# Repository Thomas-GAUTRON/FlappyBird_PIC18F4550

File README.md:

# Projet Flappy Bird PIC18F4550
Membre du projet:
 - BEAUGEANT Clément 
 - CHAUDEMANCHE Nicolas
 - COLIN Malo
 - GAUTRON Thomas 

##  Description du projet
Flappic-Bird est une réimplémentation du jeu **Flappy Bird** sur une carte de développement **EasyPIC v7**. Le jeu utilise plusieurs capteurs pour contrôler le mouvement de l’oiseau et affiche l’interface graphique via une communication UART entre la carte et un PC.

### Objectifs
- Implémenter les mécaniques de base du jeu (gravité, saut, détection de collisions).
- Comparer la précision et le temps de réponse de différents capteurs :
  - Encodeur numérique
  - Bouton poussoir
  - Capteur à ultrasons (HC-SR04)
  - Capteur infrarouge (IR Distance Click)
- Développer une interface graphique en Python
- Enregistrer les meilleurs scores en EEPROM.
- Mode "replay" pour revivre la dernière partie.

## Fonctionnalités
- **4 modes de contrôle** (encodeur, bouton, ultrasons, IR).
- **Menu interactif** (Jouer, Instructions, Replay).
- **Affichage du score** sur des affichages 7-segments et un buzzer.
- **Communication USB** entre la carte EasyPIC et le PC.
- **Mode replay** pour visualiser la dernière partie en accéléré.
- **Aspect ratio** étudié pour optimiser l’apprentissage d’un algorithme génétique (NEAT).

## 🛠 Matériel requis
- **Carte EasyPIC v7** ([manuel](https://download.mikroe.com/documents/full-featured-boards/easy/easypic-v7/easypic-v7-manual-v104c.pdf))
- **Capteurs** :
  - Encodeur numérique
  - Bouton poussoir
  - HC-SR04 (ultrasons)
  - IR Distance Click ([lien](https://www.mikroe.com/ir-distance-click))
- **Affichage** :
  - GLCD (pour l’angle de l’oiseau)
  - 7-segments (pour le score)
- **Buzzer** pour les effets sonores.
- **PC** pour l’interface graphique (Python).

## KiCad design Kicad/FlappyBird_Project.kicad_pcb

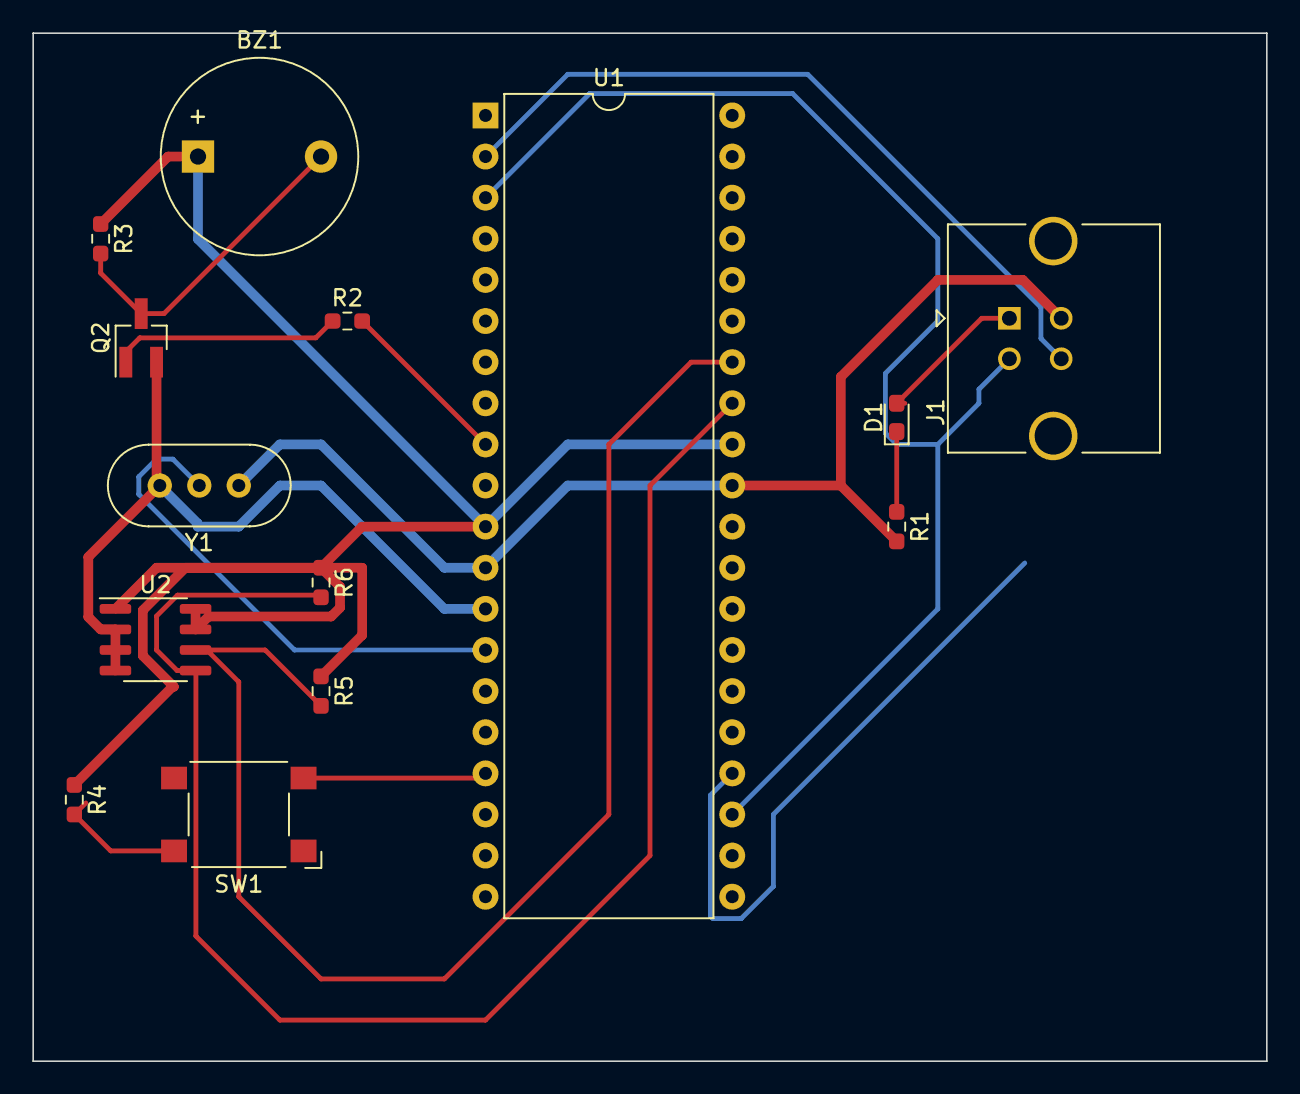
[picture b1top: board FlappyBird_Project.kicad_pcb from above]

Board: 2 copper layers, 76.2 x 63.5 mm, 14 parts (0 on the bottom side), 14 nets.

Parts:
BZ1: Buzzer; Buzzer_12x9.5RM7.6
D1: LED; LED_0603_1608Metric_Pad1.05x0.95mm_HandSolder
J1: USB_B; USB_B_Amphenol_MUSB-D511_Vertical_Rugged
Q2: BC846; SOT-23_Handsoldering
R1: 4K7; R_0603_1608Metric_Pad0.98x0.95mm_HandSolder
R2: 10K; R_0603_1608Metric_Pad0.98x0.95mm_HandSolder
R3, R5, R6: 1K; R_0603_1608Metric_Pad0.98x0.95mm_HandSolder
R4: 220; R_0603_1608Metric_Pad0.98x0.95mm_HandSolder
SW1: SW_Omron_B3FS; SW_SPST_Omron_B3FS-100xP
U1: PIC18F4550-IP; DIP-40_W15.24mm
U2: M24C02-WMN; SOIC-8_3.9x4.9mm_P1.27mm
Y1: Crystal_GND3; Crystal_HC49-U-3Pin_Vertical

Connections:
GND: J1.4 (GND), Q2.2 (E), R1.2, U1.12 (VSS), U1.13 (OSC1/CLKI), U1.31 (VSS), U2.2 (E1), U2.3 (E2), U2.4 (VSS), Y1.1, Y1.3
unnamed: BZ1.2 (+), Q2.3 (C), R3.2
unnamed: D1.2 (A), J1.1 (VBUS)
unnamed: D1.1 (K), R1.1
unnamed: J1.3 (D+), U1.2 (RA0/AN0), U1.24 (VP/D+/RC5)
unnamed: J1.2 (D-), U1.3 (RA1/AN1), U1.23 (VM/D-/RC4)
unnamed: Q2.1 (B), R2.1
unnamed: R4.2, SW1.1
unnamed: R2.2, U1.9 (CK2SPP/AN6/RE1)
unnamed: SW1.2, U1.17 (P1A/CCP1/RC2)
unnamed: U1.14 (RA6/OSC2/CLKO), Y1.2
unnamed: R6.2, U1.33 (RB0/AN12/INT0/FLT0/SDI/SDA), U2.5 (SDA)
unnamed: R5.2, U1.34 (RB1/AN10/INT1/SCK/SCL), U2.6 (SCL)
VCC: BZ1.1 (-), R3.1, R4.1, R5.1, R6.1, U1.11 (VDD), U1.32 (VDD), U2.1 (E0), U2.7 (~WC), U2.8 (VCC)

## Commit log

2025-10-16 Init Projet
2025-10-16 Ajout de la communication USB
2025-10-17 PushButtonNoRebound
    full .asm PushButtonNoRebound, à adapter pour le C
2025-10-17 Rename pushbutton to pushbutton.asm
2025-10-17 Update pushbutton.asm
    flag mis à levé sur appui bouton, plus sur appui->relachement
2025-10-17 Update pushbutton.asm
    ajout d'une interruption haute priorité
2025-10-18 Changelog : Ajout du bouton poussoir
2025-10-18 Ajout des ficher kicad dans le dossier kicad
2025-10-18 Màj du Readme
2025-10-18 Ajout du code de base de flappy
2025-10-18 Ajout code base flappy
2025-10-19 Add files via upload
    interface_pc
2025-10-19 Intégration entre le pic18f et la v2 du flappy - Potentiomètre pour selectionner dans le menu - Bouton B0 pour tous les cliques - Affichage sur score sur les 7 segments
2025-10-19 Ajout de l'ago sur daw.io
2025-10-19 Suppression du Changlog
2025-10-22 Enlever les fichier inutile
2025-10-22 Déplacer le fichier draw.io
2025-10-22 Ajout du template du rapport
2025-10-22 Modification du fonctionnement des 7 segs
2025-11-03 Rapport v1
2025-11-04 Ajout de l'écran glcd
2025-11-05 Create InfrarougeRC2.c
    Ajout de l'option infrarouge, sur RC2
2025-11-05 Ajout eeprom + infrarouge
2025-11-07 Ajout infrarouge python
2025-11-07 debug du code avant ajout du ultrason
2025-11-07 Ajout ultrason et mouvement sur le glcd
2025-11-08 Ajout ultrason + ou - Ajout de la conf de + de bouton entre le python et le PIC
2025-11-08 WIP: mes modifs
2025-11-08 Ajout ultra-son
2025-11-09 Amélioration ultrason Sélection automatique du COM Ajout du quit dans la sélection des modes
2025-11-09 WIP: mes modifs
    :/Users/maloc/AppData/Local/Programs/Python/Python311/python.exe
    c:/Users/maloc/Documents/02_ECE/PROJETS/ING4_MCU_Projet/GitHubProject/FlappyBird_PIC18F4550/pc/main.py
    :/Users/maloc/AppData/Local/Programs/Python/Python311/python.exe
    c:/Users/maloc/Documents/02_ECE/PROJETS/ING4_MCU_Projet/GitHubProject/FlappyBird_PIC18F4550/pc/main.py
    .git/COMMIT_EDITMSG [unix] (12:52 09/11/2025) 1,1 Top
    "~/Documents/02_ECE/PROJETS/ING4_MCU_Projet/GitHubProject/FlappyBird_PIC18F4550/.git/COMMIT_
2025-11-09 Debug du jeu python
2025-11-09 Débug bird
2025-11-09 Débug de mise à jours du meilleur score
2025-11-09 ajout best score 4modes
2025-11-09 Ajout connextion meilleur score EEPROM
2025-11-09 Débug meilleur score
2025-11-09 mode info maj
2025-11-09 Dernière petite modif
2025-11-09 derniere modif
2025-11-09 LAST COMMIT
2025-11-09 renderer
